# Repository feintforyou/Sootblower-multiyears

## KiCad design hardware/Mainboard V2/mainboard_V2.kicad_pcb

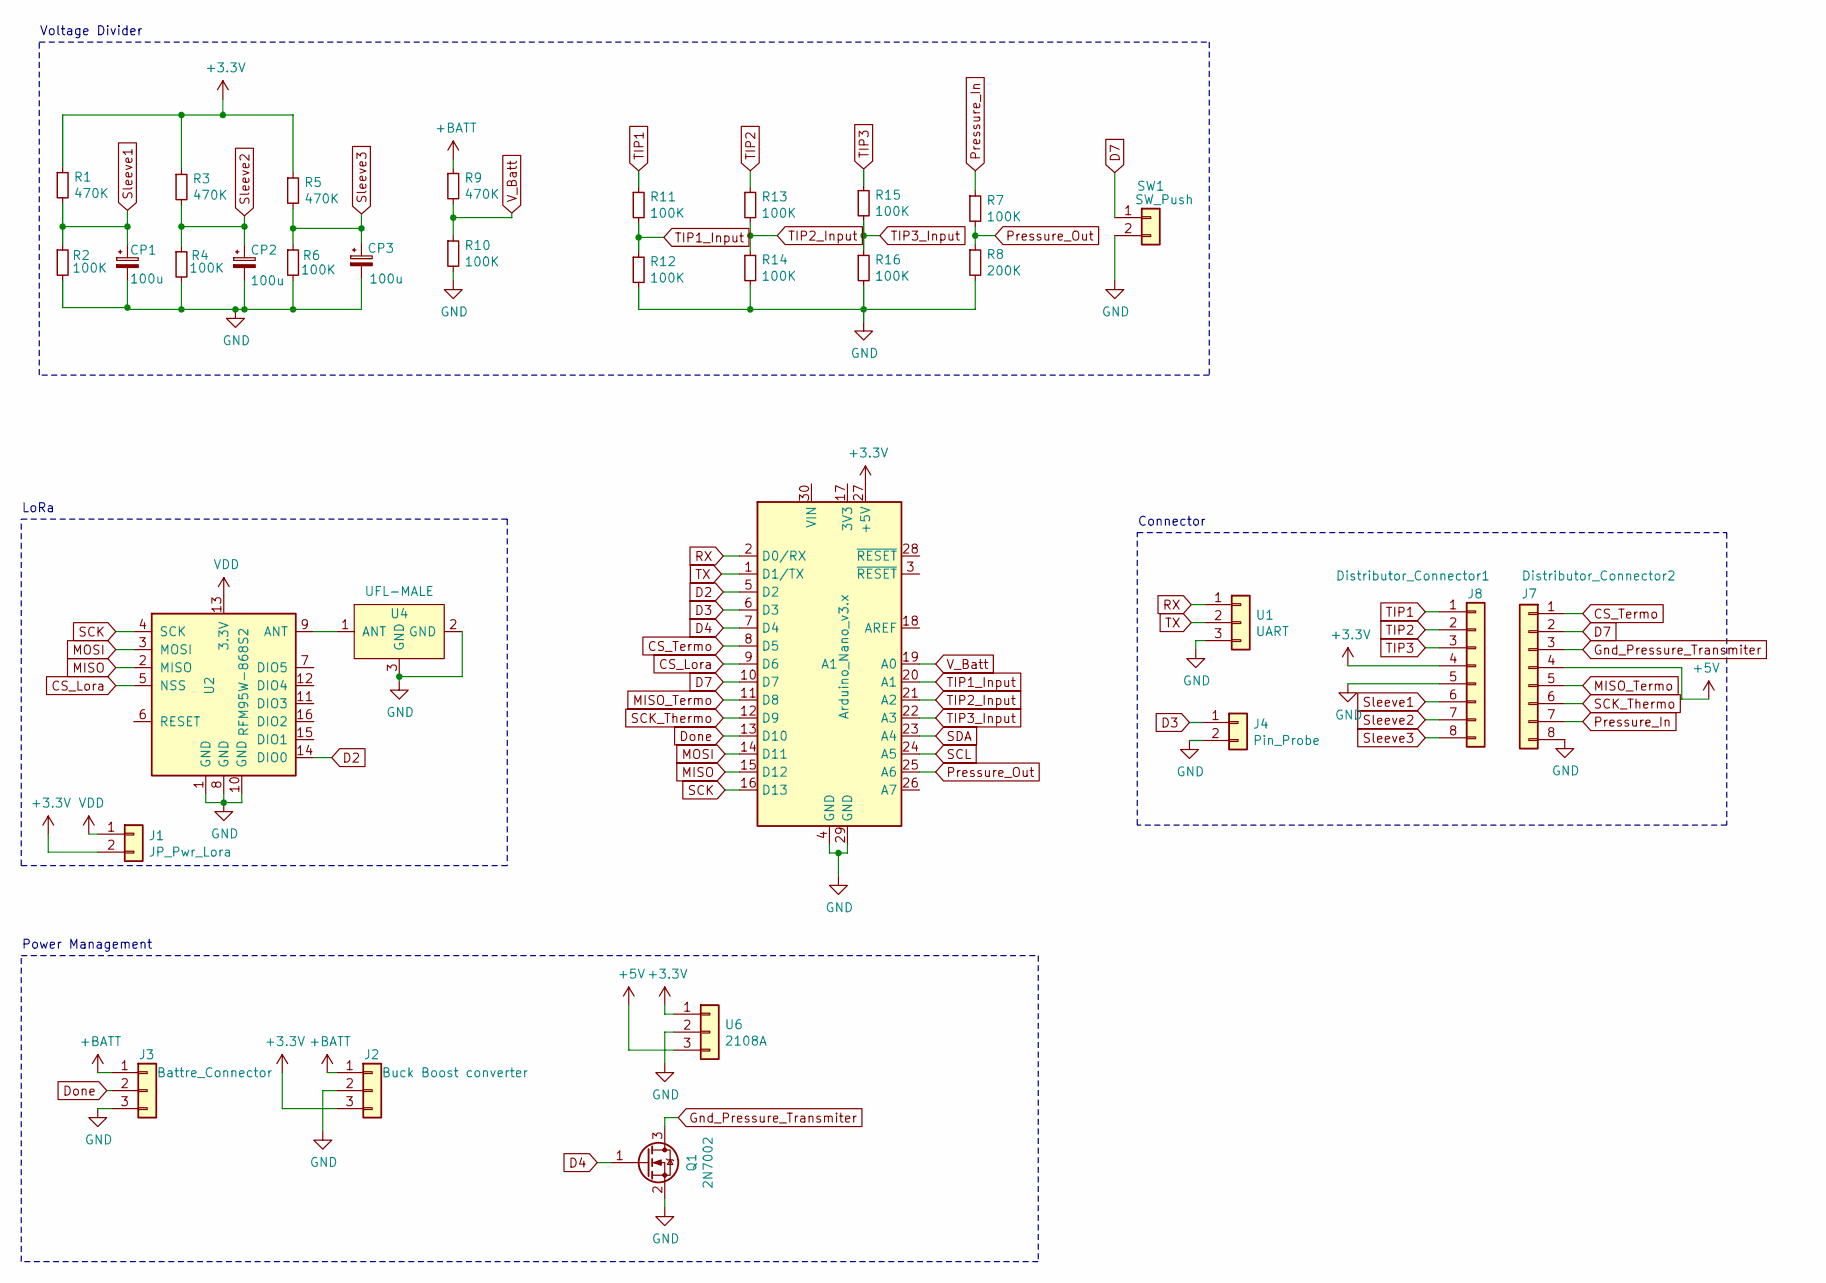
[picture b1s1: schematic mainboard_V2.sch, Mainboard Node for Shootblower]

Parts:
A1: Arduino_Nano_v3.x; Arduino_Nano
CP1, CP2, CP3: 100u; CP_Radial_D5.0mm_P2.50mm
J1: JP_Pwr_Lora; PinHeader_1x02_P2.54mm_Vertical
J2: Buck Boost converter; PinHeader_1x03_P2.54mm_Vertical
J3: Battre_Connector; JST_XH_B3B-XH-A_1x03_P2.50mm_Vertical
J4: Pin_Probe; PinHeader_1x02_P2.54mm_Vertical
J7: Distributor_Connector2; Molex_KK-254_AE-6410-08A_1x08_P2.54mm_Vertical
J8: Distributor_Connector1; Molex_KK-254_AE-6410-08A_1x08_P2.54mm_Vertical
Q1: 2N7002; PinHeader_1x03_P2.54mm_Vertical
R1, R3, R5, R9: 470K; R_Axial_DIN0207_L6.3mm_D2.5mm_P10.16mm_Horizontal
R2, R4, R6, R7, R10, R11, R12, R13, R14, R15, R16: 100K; R_Axial_DIN0207_L6.3mm_D2.5mm_P10.16mm_Horizontal
R8: 200K; R_Axial_DIN0207_L6.3mm_D2.5mm_P10.16mm_Horizontal
SW1: SW_Push; PinHeader_1x02_P2.54mm_Vertical
U1: UART; PinHeader_1x03_P2.54mm_Vertical
U2: RFM95W-868S2; HOPERF_RFM9XW_THT
U4: UFL-MALE; UFL-Male
U6: 2108A; PinHeader_1x03_P2.54mm_Vertical

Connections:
+3V3: A1.27 (+5V), J1.2, J2.3, J8.4, R1.1, R3.1, R5.1, U6.1
+5V: J7.4, U6.3
+BATT: J2.1, J3.1, R9.1
CS_Lora: A1.9 (D6), U2.5 (NSS)
CS_Termo: A1.8 (D5), J7.1
D2: A1.5 (D2), U2.14 (DIO0)
D3: A1.6 (D3), J4.1
D4: A1.7 (D4), Q1.1 (G)
D7: A1.10 (D7), J7.2, SW1.1
Done: A1.13 (D10), J3.2
GND: A1.4 (GND), A1.29 (GND), CP1.2, CP2.2, CP3.2, J2.2, J3.3, J4.2, J7.8, J8.5, Q1.2 (S), R2.2, R4.2, R6.2, R8.2, R10.2, R12.2, R14.2, R16.2, SW1.2, U1.3, U2.1 (GND), U2.8 (GND), U2.10 (GND), U4.2 (GND), U4.3 (GND), U6.2
Gnd_Pressure_Transmiter: J7.3, Q1.3 (D)
MISO: A1.15 (D12), U2.2 (MISO)
MISO_Termo: A1.11 (D8), J7.5
MOSI: A1.14 (D11), U2.3 (MOSI)
unnamed: U2.9 (ANT), U4.1 (ANT)
Pressure_In: J7.7, R7.1
Pressure_Out: A1.25 (A6), R7.2, R8.1
RX: A1.2 (D0/RX), U1.1
SCK: A1.16 (D13), U2.4 (SCK)
SCK_Thermo: A1.12 (D9), J7.6
SCL: A1.24 (A5)
SDA: A1.23 (A4)
Sleeve1: CP1.1, J8.6, R1.2, R2.1
Sleeve2: CP2.1, J8.7, R3.2, R4.1
Sleeve3: CP3.1, J8.8, R5.2, R6.1
TIP1: J8.1, R11.1
TIP1_Input: A1.20 (A1), R11.2, R12.1
TIP2: J8.2, R13.1
TIP2_Input: A1.21 (A2), R13.2, R14.1
TIP3: J8.3, R15.1
TIP3_Input: A1.22 (A3), R15.2, R16.1
TX: A1.1 (D1/TX), U1.2
VDD: J1.1, U2.13 (3.3V)
V_Batt: A1.19 (A0), R9.2, R10.1

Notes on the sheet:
Connector
LoRa
Voltage Divider
Power Management

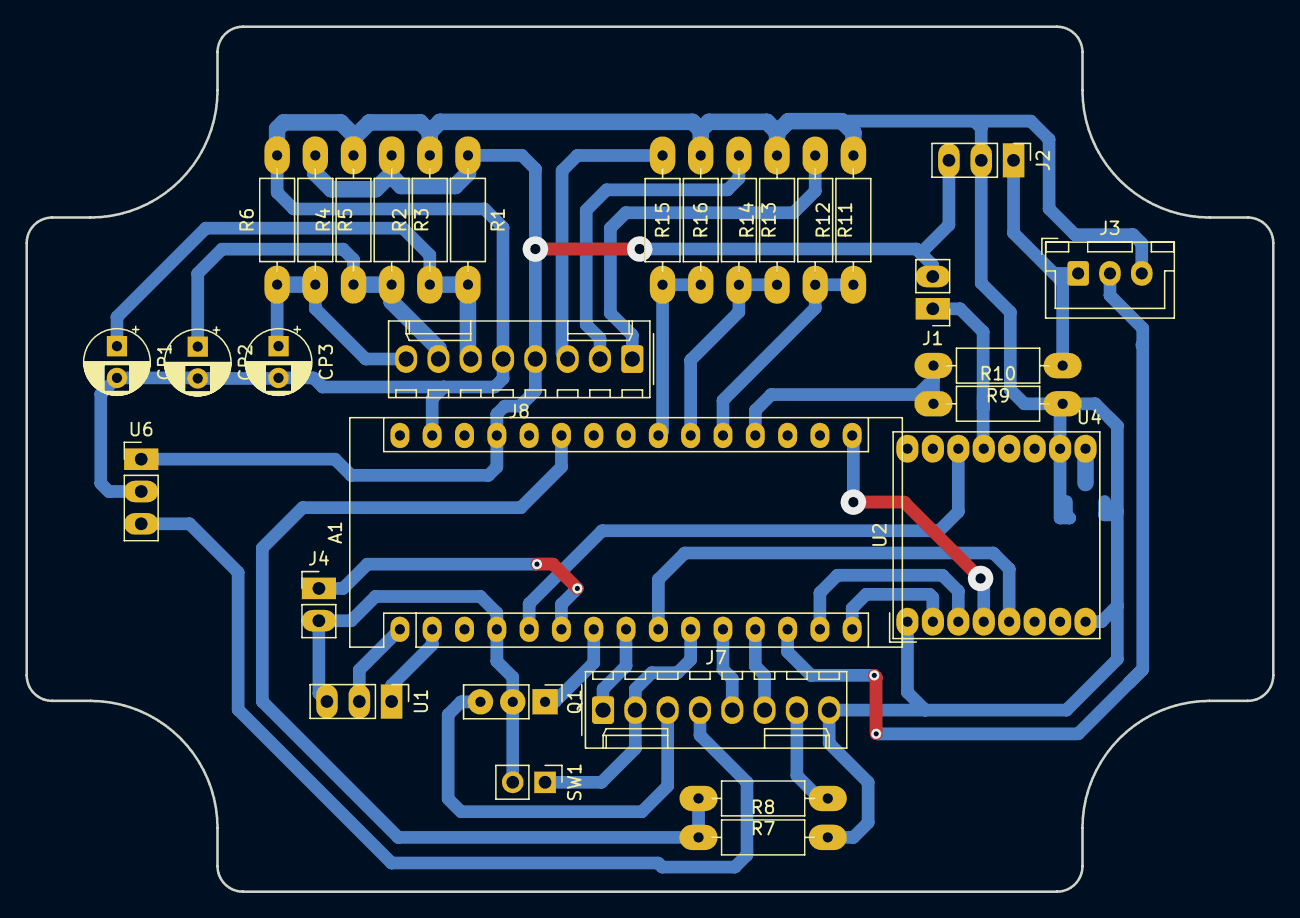
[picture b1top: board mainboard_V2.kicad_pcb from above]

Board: 2 copper layers, 98.0 x 68.0 mm, 32 parts (0 on the bottom side), 33 nets.

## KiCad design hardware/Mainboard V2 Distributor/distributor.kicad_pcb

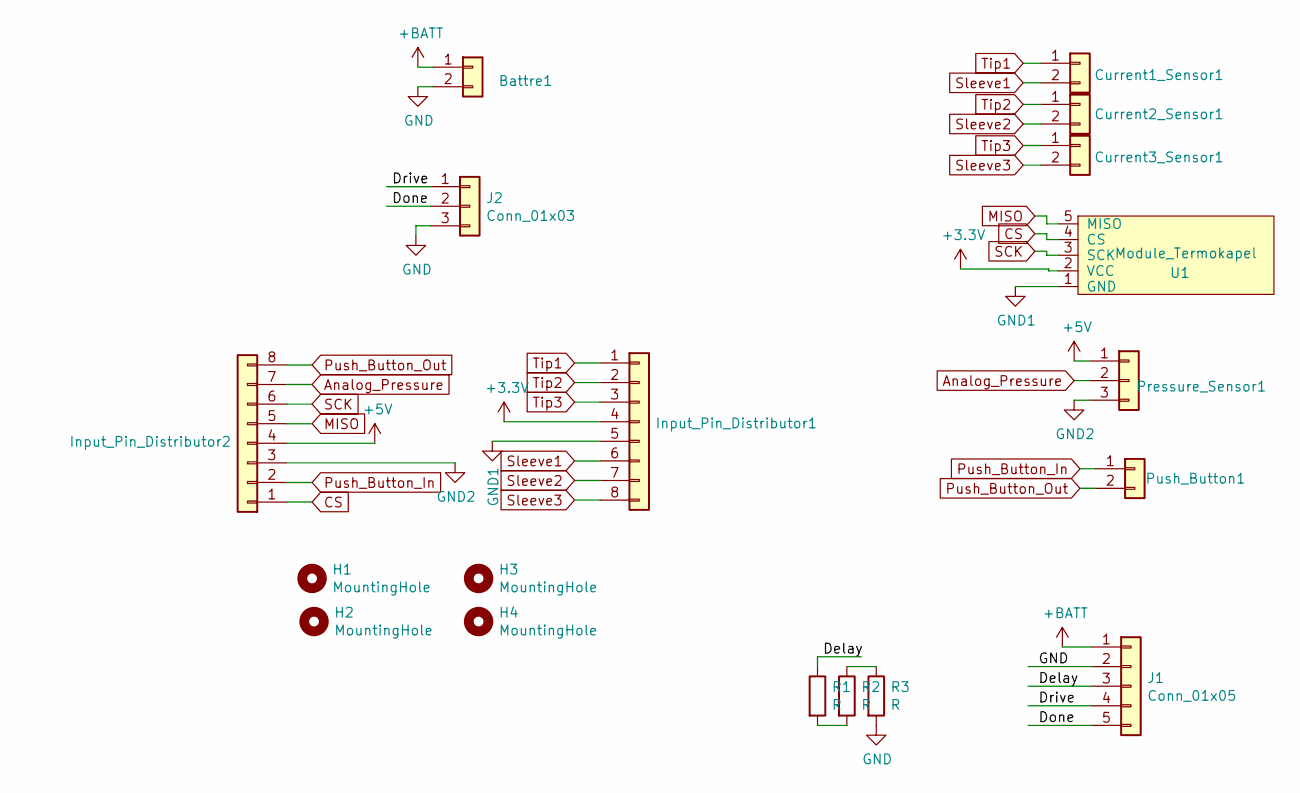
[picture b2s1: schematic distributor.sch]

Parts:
Battre1: TerminalBlock_Phoenix_MKDS-1,5-2-5.08_1x02_P5.08mm_Horizont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
Current1_Sensor1, Current2_Sensor1, Current3_Sensor1: TerminalBlock_Phoenix_MKDS-1,5-2-5.08_1x02_P5.08mm_Horizont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
H1, H2, H3, H4: MountingHole; MountingHole_3.2mm_M3
Input_Pin_Distributor1, Input_Pin_Distributor2: Molex_KK-254_AE-6410-08A_1x08_P2.54mm_Vertical
J1: Conn_01x05; PinSocket_1x05_P2.54mm_Vertical
J2: Conn_01x03; JST_XH_B3B-XH-A_1x03_P2.50mm_Vertical
Pressure_Sensor1: TerminalBlock_Phoenix_MKDS-1,5-3-5.08_1x03_P5.08mm_Horizont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
Push_Button1: TerminalBlock_Phoenix_MKDS-1,5-2-5.08_1x02_P5.08mm_Horizont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
R1, R2, R3: R; R_Axial_DIN0207_L6.3mm_D2.5mm_P10.16mm_Horizontal
U1: Module_Termokapel; Modul Termokapel

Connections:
+3V3: Input_Pin_Distributor1.4, U1.2 (VCC)
+5V: Input_Pin_Distributor2.4, Pressure_Sensor1.1
+BATT: Battre1.1, J1.1
/Delay: J1.3, R1.1
/Done: J1.5, J2.2
/Drive: J1.4, J2.1
Analog_Pressure: Input_Pin_Distributor2.7, Pressure_Sensor1.2
CS: Input_Pin_Distributor2.1, U1.4 (CS)
GND: Battre1.2, J1.2, J2.3, R3.2
GND1: Input_Pin_Distributor1.5, U1.1 (GND)
GND2: Input_Pin_Distributor2.3, Pressure_Sensor1.3
MISO: Input_Pin_Distributor2.5, U1.5 (MISO)
unnamed: R1.2, R2.2
unnamed: R2.1, R3.1
Push_Button_In: Input_Pin_Distributor2.2, Push_Button1.1
Push_Button_Out: Input_Pin_Distributor2.8, Push_Button1.2
SCK: Input_Pin_Distributor2.6, U1.3 (SCK)
Sleeve1: Current1_Sensor1.2, Input_Pin_Distributor1.6
Sleeve2: Current2_Sensor1.2, Input_Pin_Distributor1.7
Sleeve3: Current3_Sensor1.2, Input_Pin_Distributor1.8
Tip1: Current1_Sensor1.1, Input_Pin_Distributor1.1
Tip2: Current2_Sensor1.1, Input_Pin_Distributor1.2
Tip3: Current3_Sensor1.1, Input_Pin_Distributor1.3

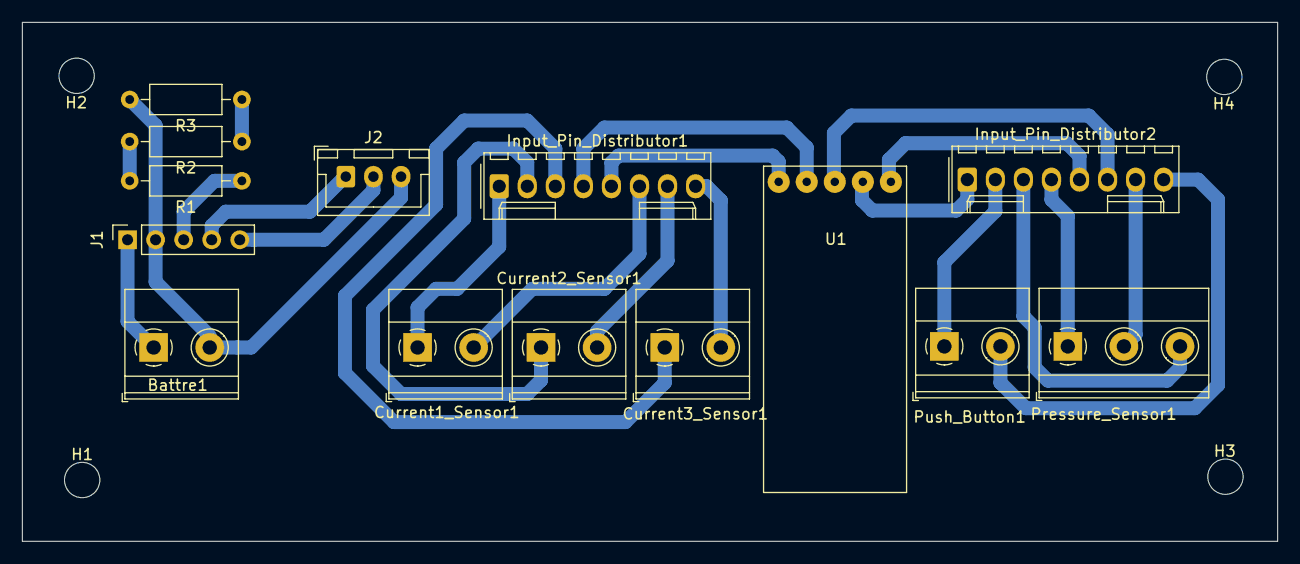
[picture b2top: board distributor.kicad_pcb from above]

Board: 2 copper layers, 113.7 x 47.0 mm, 18 parts (0 on the bottom side), 23 nets.

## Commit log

2021-09-17 add hardware file
